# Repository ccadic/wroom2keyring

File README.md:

# wroom2keyring
This is a small ESP32 Keyring PCB
With schematic and software

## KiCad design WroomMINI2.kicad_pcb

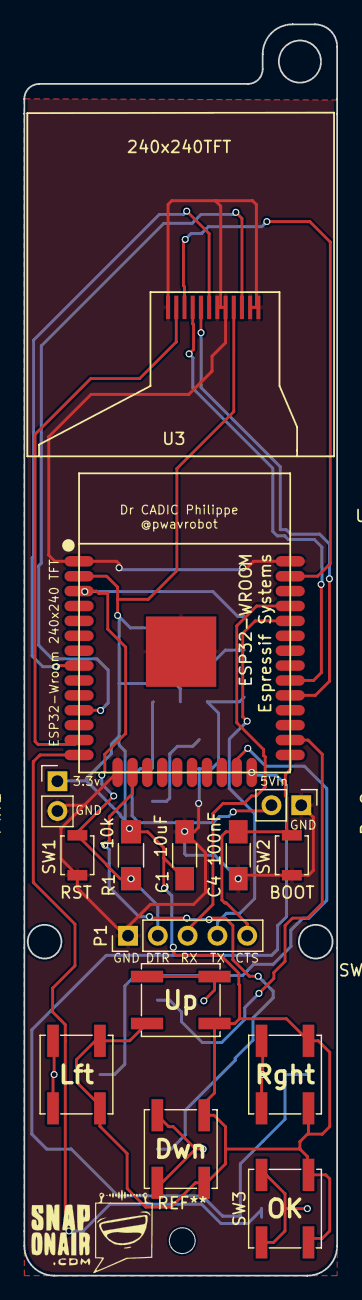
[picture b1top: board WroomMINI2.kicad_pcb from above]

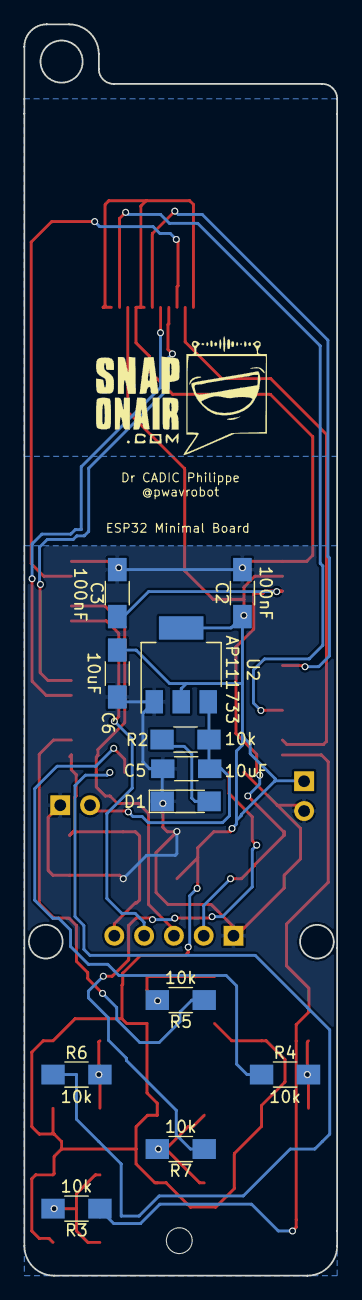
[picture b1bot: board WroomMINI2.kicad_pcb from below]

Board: 2 copper layers, 26.7 x 106.7 mm, 27 parts (12 on the bottom side), 24 nets.

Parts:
C1, C5, C6: 10uF; C_1206_HandSoldering
C2, C3, C4: 100nF; C_1206_HandSoldering
D1: PowerOn; LED_1206_HandSoldering
P1: ProgHeader; Socket_Strip_Straight_1x05_Pitch2.54mm
Pwr1: Pwr; Socket_Strip_Straight_1x02_Pitch2.54mm
Pwr2: 5Vin; Socket_Strip_Straight_1x02_Pitch2.54mm
R1, R2, R3, R4, R5, R6, R7: 10k; R_1206_HandSoldering
SW1: RST; SW_SPST_B3U-1000P
SW2: BOOT; SW_SPST_B3U-1000P
SW3: OK; SW_SPST_EVQP0
SW4: L; SW_SPST_EVQP0
SW5: U; SW_SPST_EVQP0
SW6: R; SW_SPST_EVQP0
SW7: D; SW_SPST_EVQP0
U1: ESP32-WROOM
U2: AP111733; SOT-223
U3: 240x240TFT; 240240TFT

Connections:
+3V3: C1.1, C2.1, C6.1, Pwr1.1, R1.1, SW3.2, SW4.2, SW5.2, SW6.2, SW7.2, U1.2, U2.2, U2.4, U3.4
+5V: C5.1, Pwr2.2, R2.1, U2.3
/CLK: U1.30, U3.9
/DCDISP: U1.8, U3.7
/LEDA: U1.11, U3.3
/MOSI: U1.37, U3.10
/RESETDISP: U1.13, U3.11
/RX: P1.4, U1.34
/SPI_SS: U1.29, U3.8
/TX: P1.3, U1.35
/Touch1: R4.1, U1.23
/Touch2: R5.1, U1.26
/Touch3: R6.1, U1.24
/Touch4: R7.1, U1.16
/Touch5: R3.1, U1.14
GND: C1.2, C2.2, C3.2, C4.2, C5.2, C6.2, D1.1, P1.1, Pwr1.2, Pwr2.1, SW1.1, SW2.1, U1.1, U1.15, U1.38, U1.39, U2.1, U3.1, U3.2, U3.5, U3.6, U3.12
unnamed: C3.1, P1.2, R1.2, SW1.2, U1.3
unnamed: C4.1, P1.5, SW2.2, U1.25
unnamed: D1.2, R2.2
unnamed: R3.2, SW3.1
unnamed: R4.2, SW4.1
unnamed: R5.2, SW5.1
unnamed: R6.2, SW6.1
unnamed: R7.2, SW7.1
